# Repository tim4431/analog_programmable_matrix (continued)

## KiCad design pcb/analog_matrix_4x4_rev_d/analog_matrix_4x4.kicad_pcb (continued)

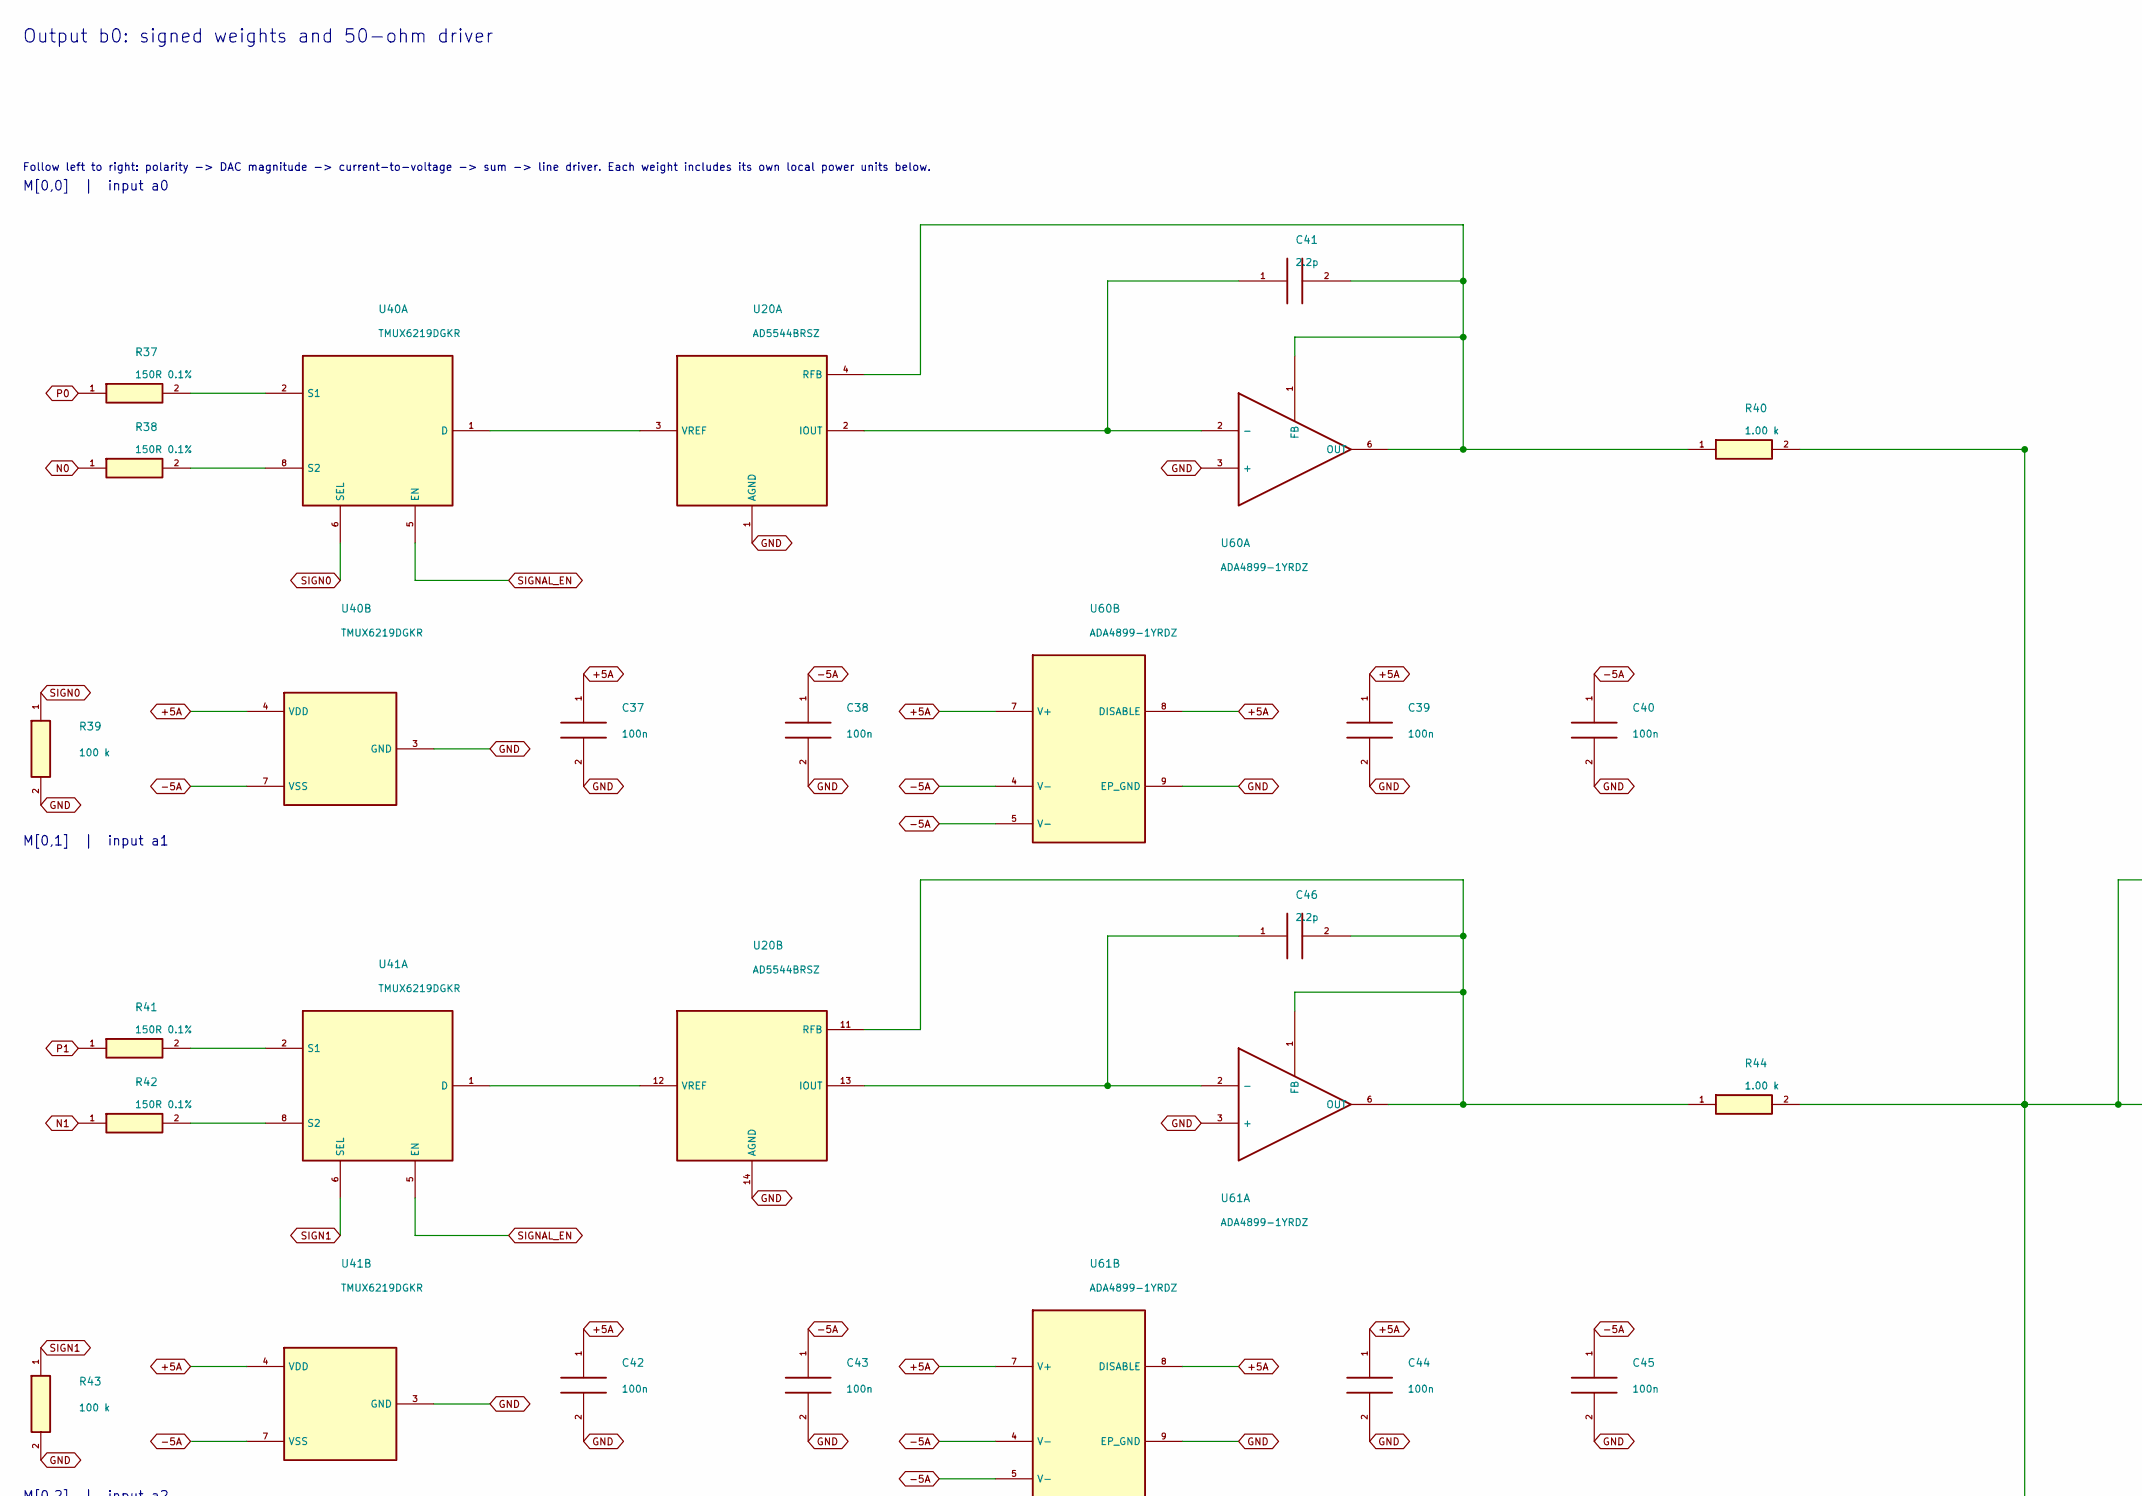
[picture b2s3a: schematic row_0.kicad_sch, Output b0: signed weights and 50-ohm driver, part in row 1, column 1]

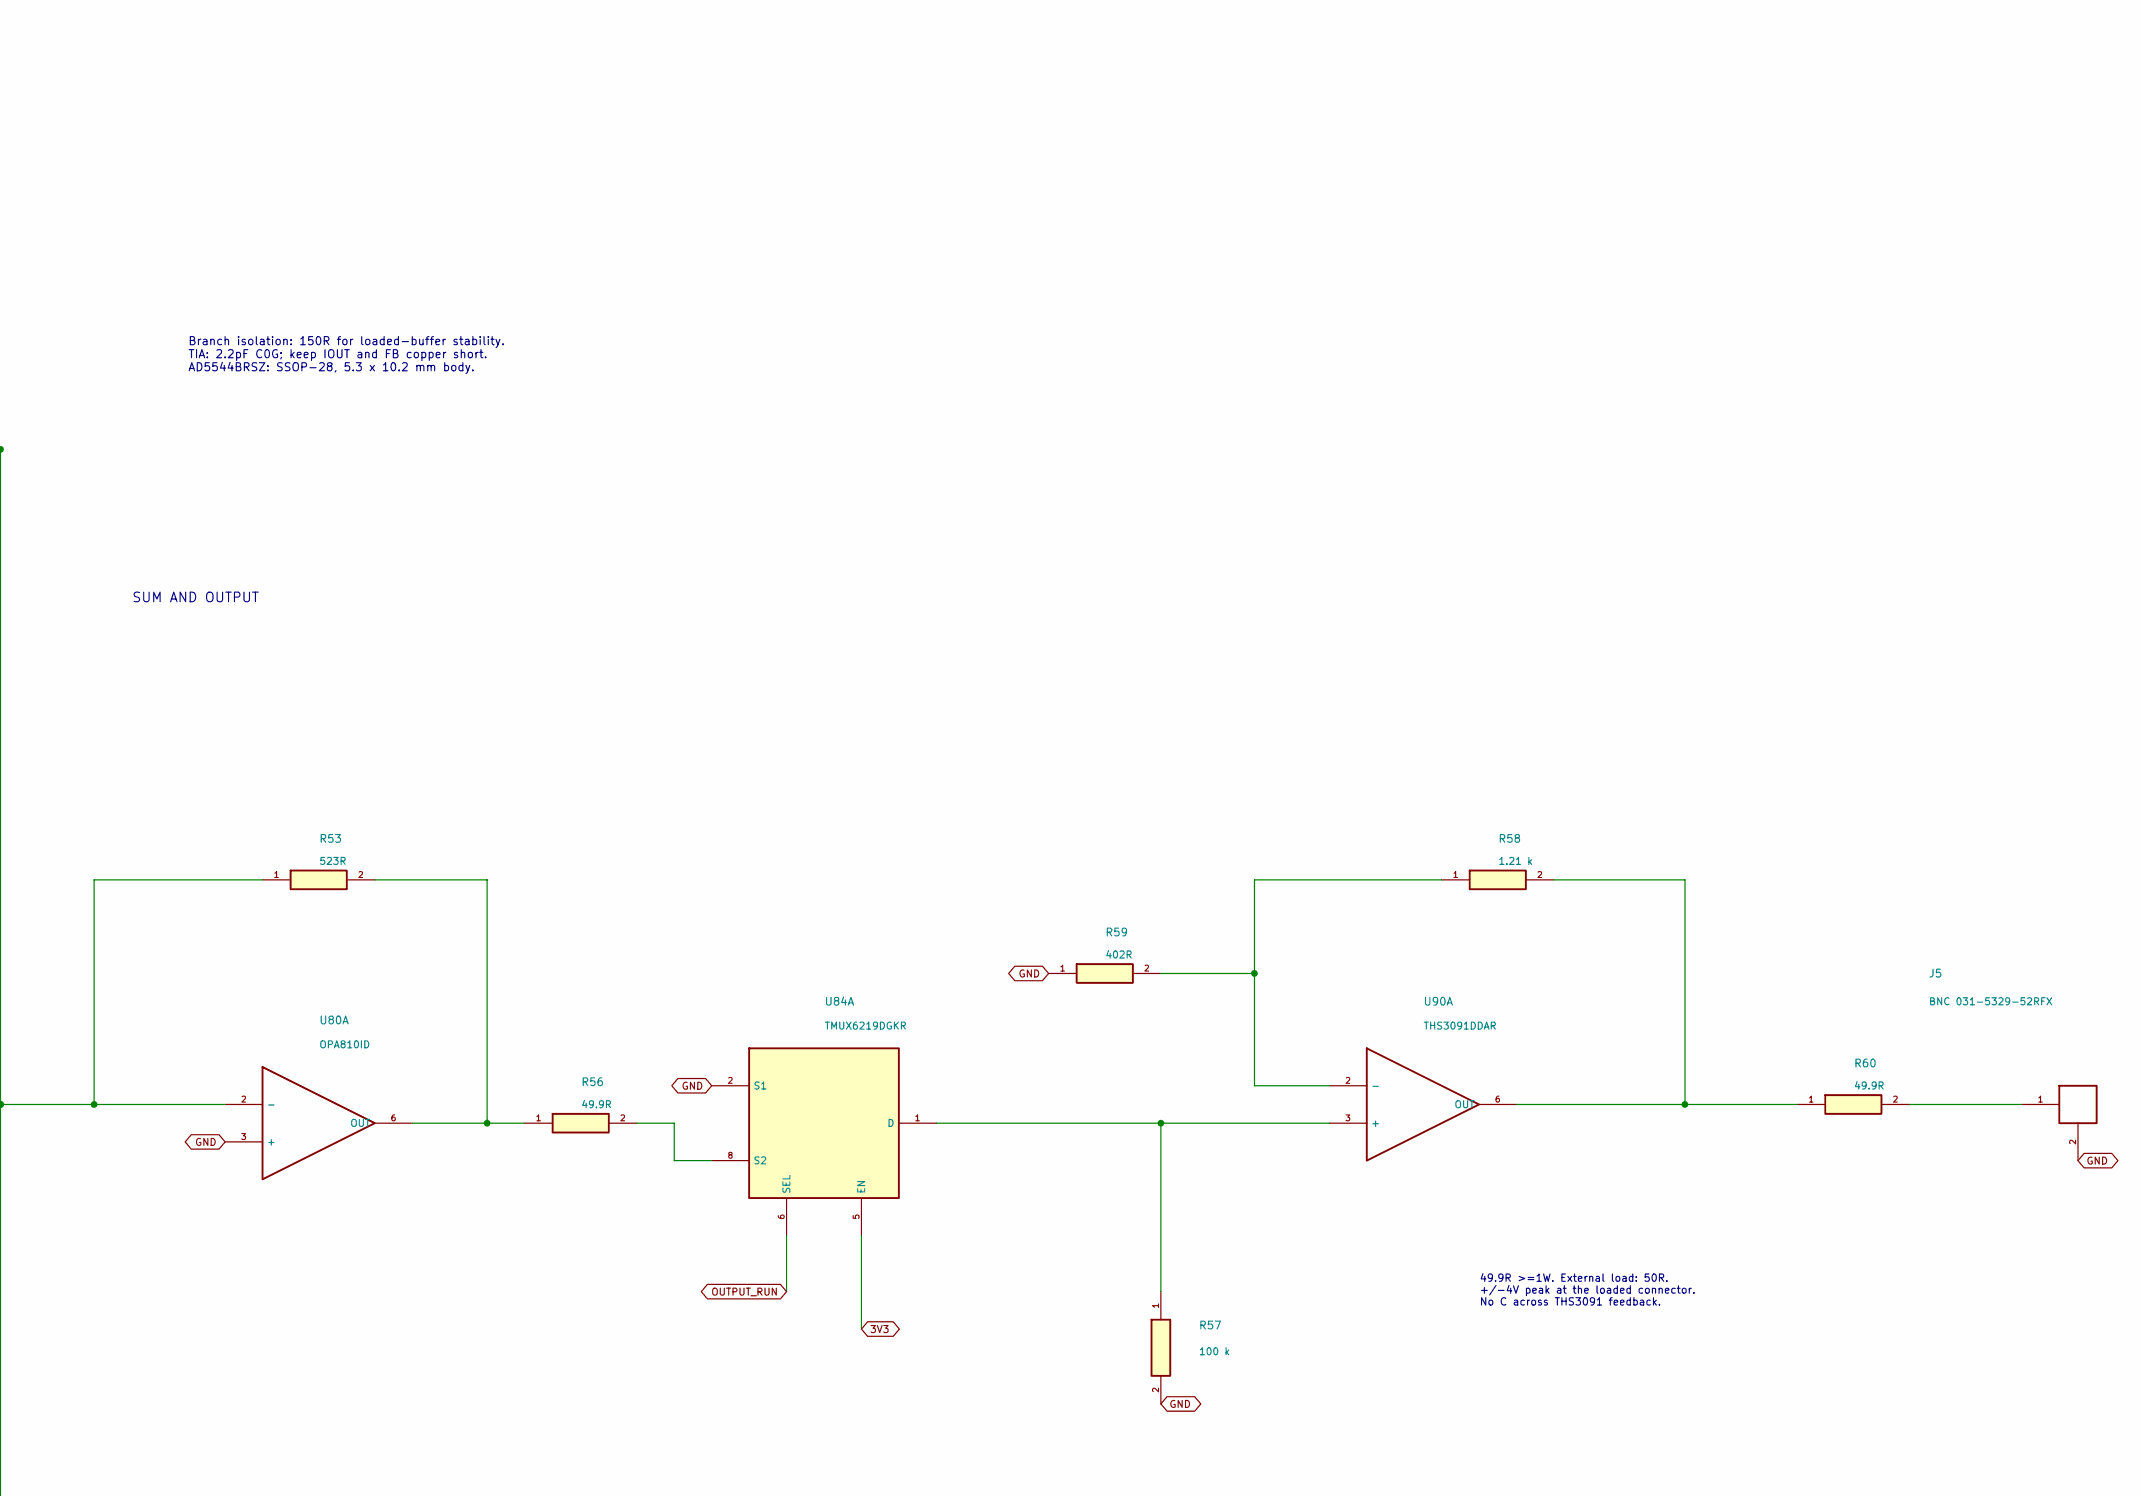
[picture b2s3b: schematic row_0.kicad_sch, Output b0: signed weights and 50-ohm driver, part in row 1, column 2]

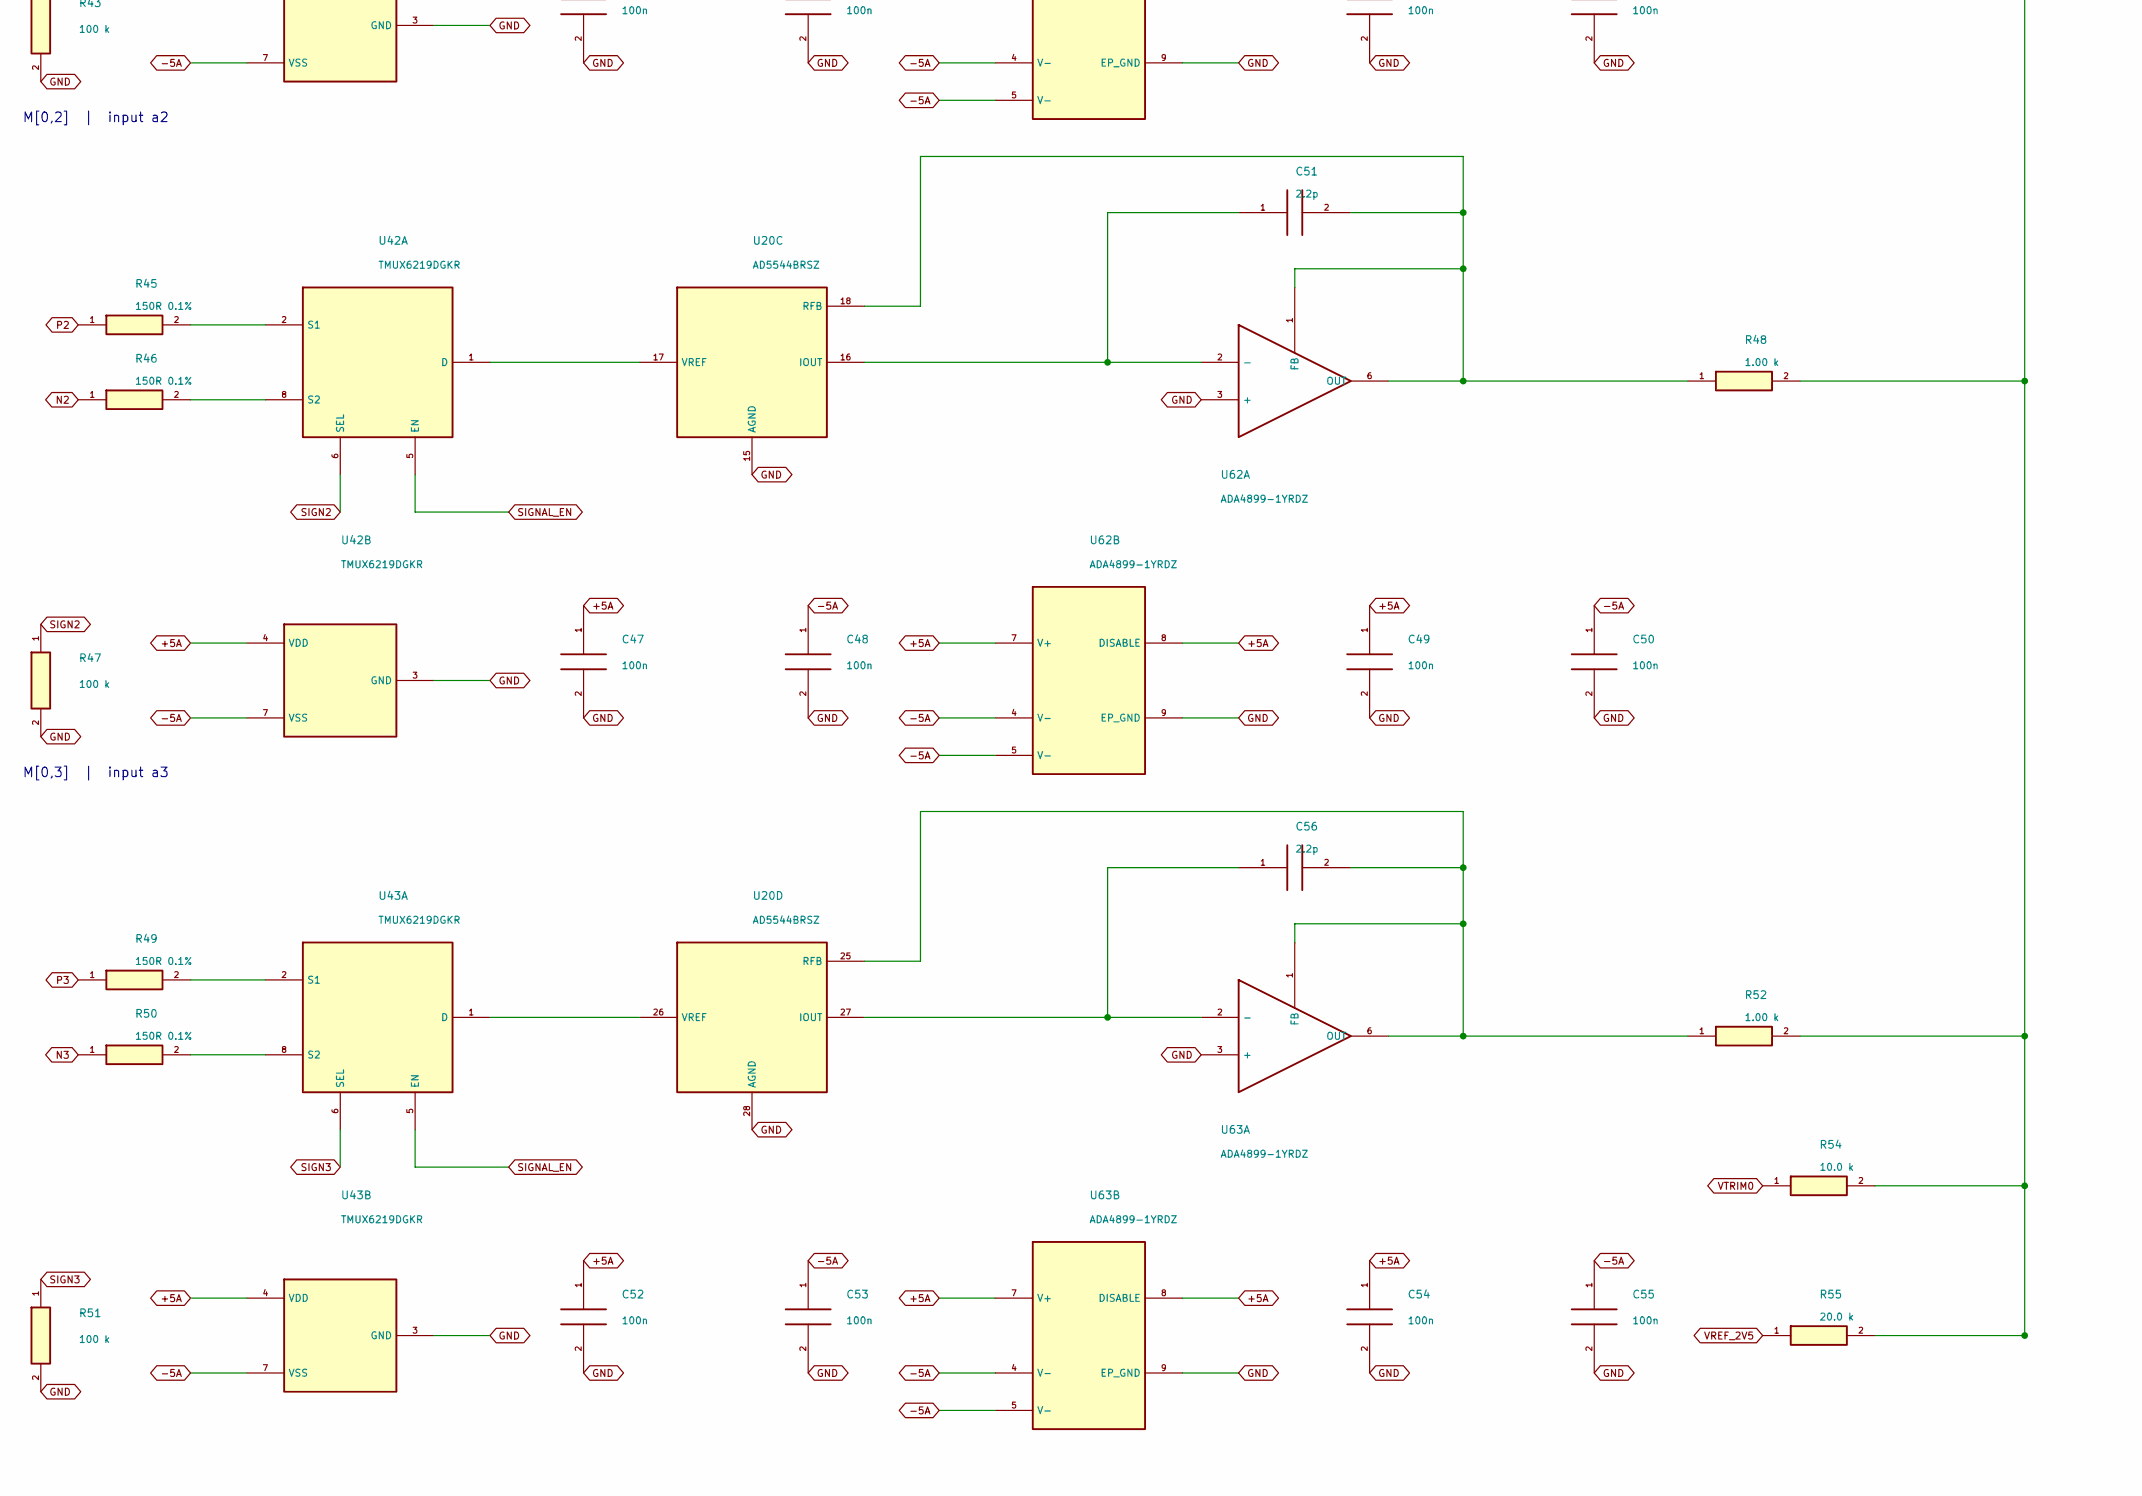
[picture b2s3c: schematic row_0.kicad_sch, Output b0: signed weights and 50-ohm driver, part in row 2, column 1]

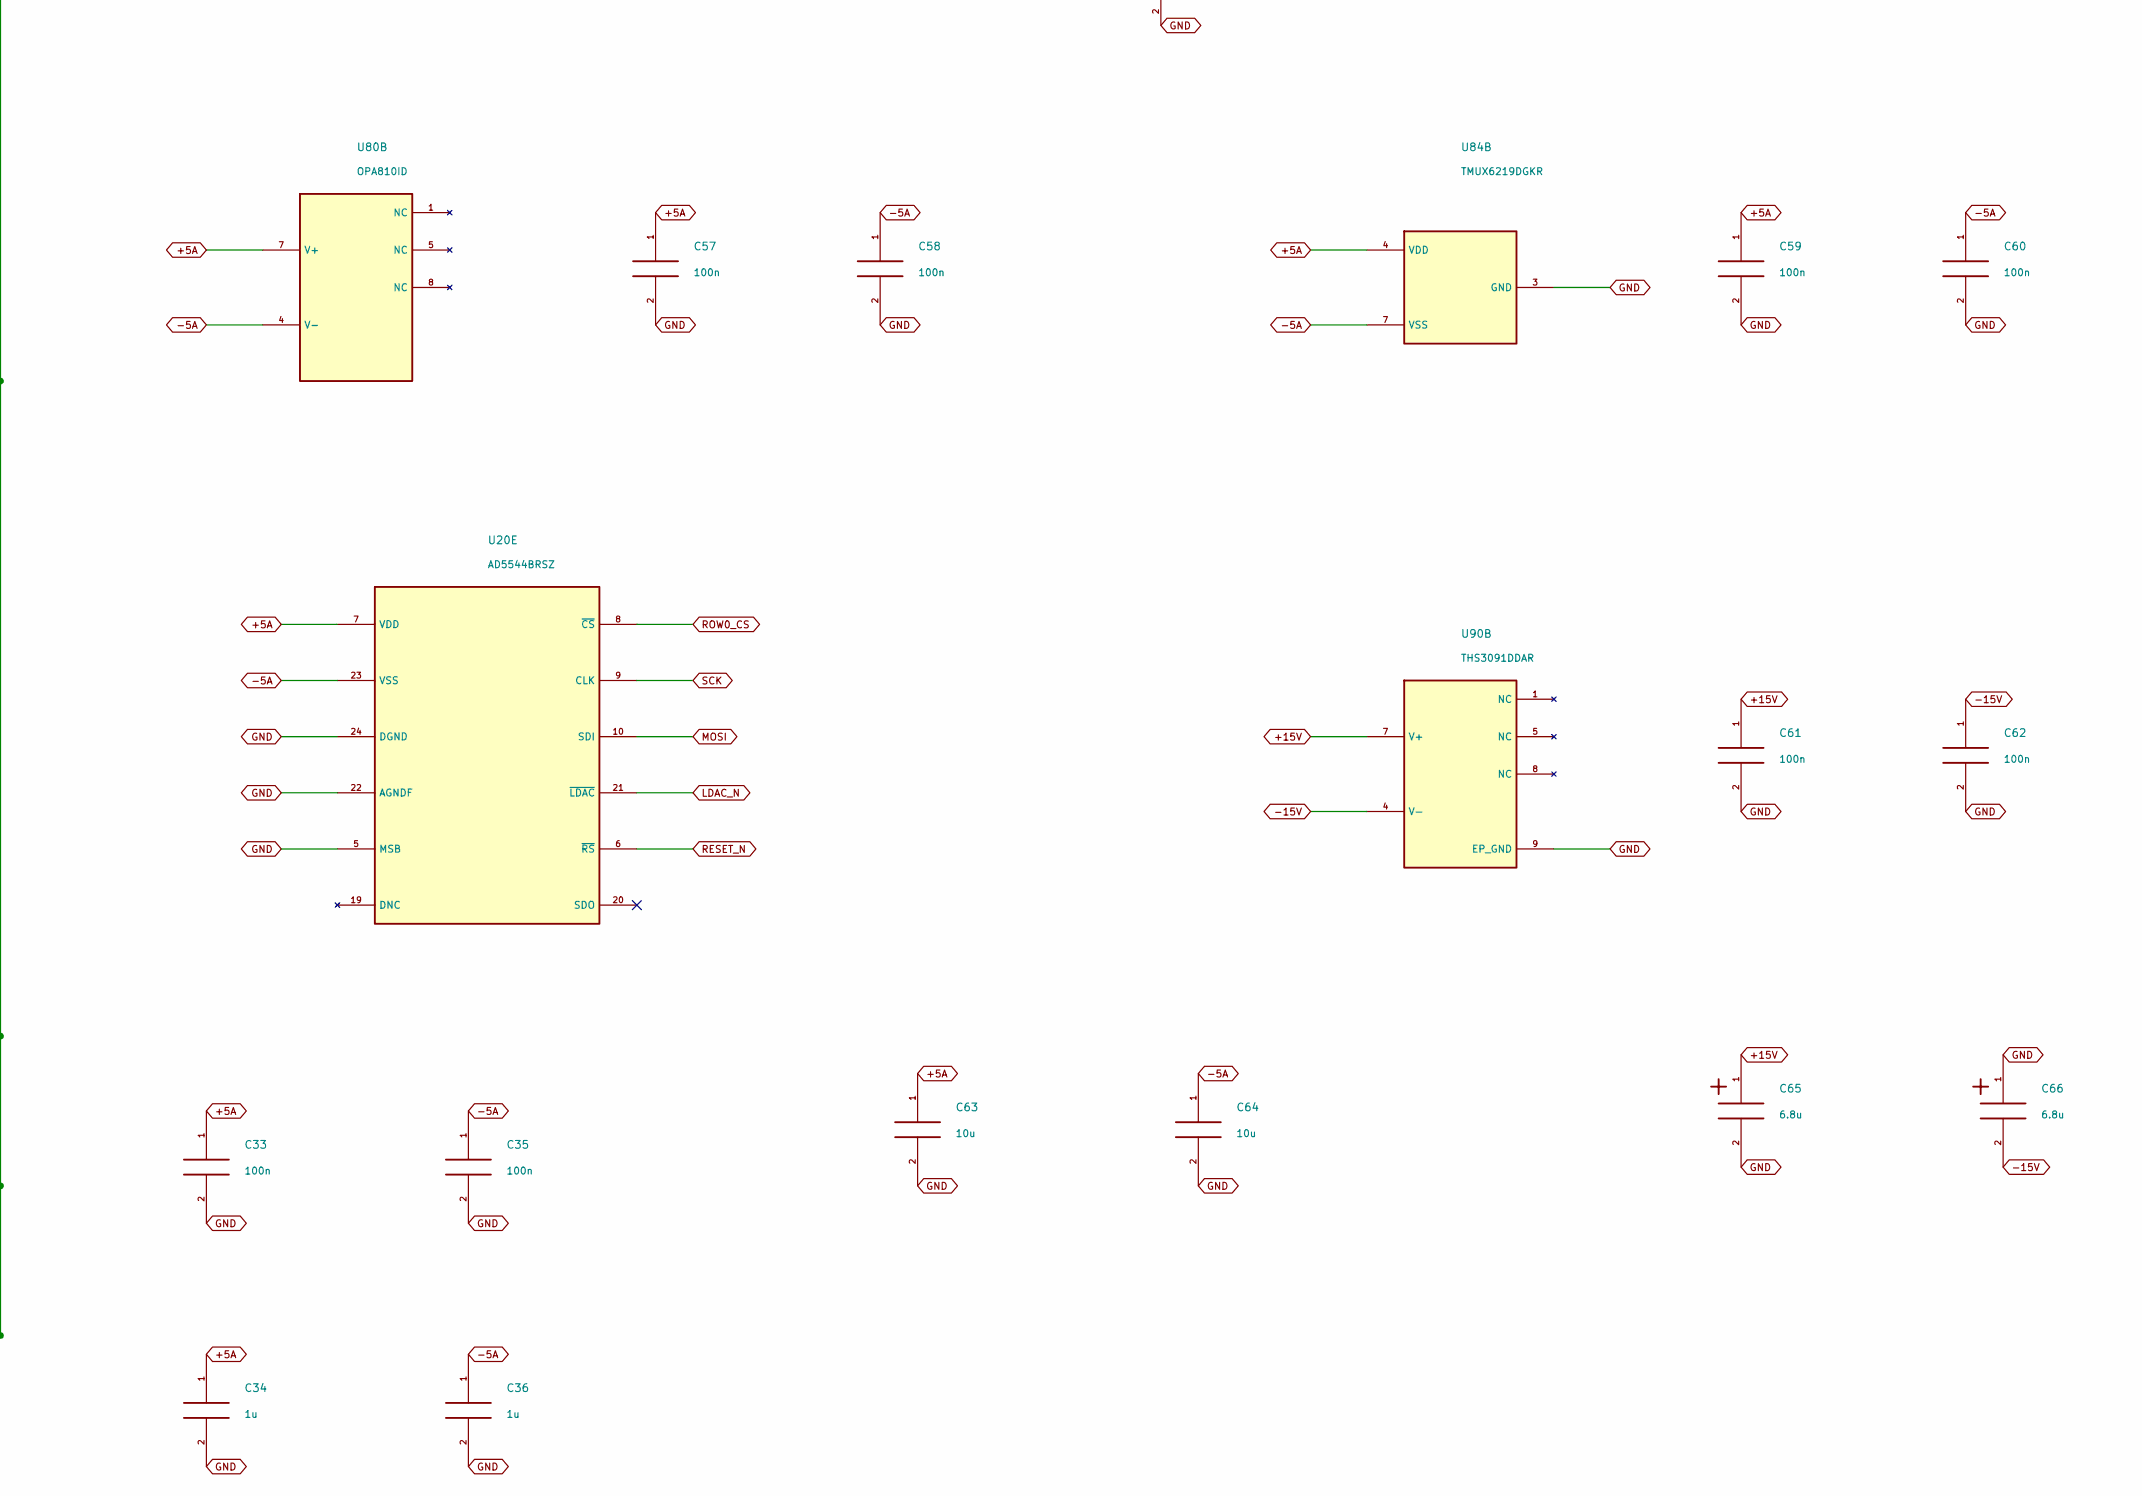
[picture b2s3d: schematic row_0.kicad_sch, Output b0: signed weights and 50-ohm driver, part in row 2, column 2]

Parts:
C33, C35, C37, C38, C39, C40, C42, C43, C44, C45, C47, C48, C49, C50, C52, C53, C54, C55, C57, C58, C59, C60, C61, C62: 100n; C_0603_1608Metric; Rating 25V X7R minimum; effective C after bias
C34, C36: 1u; C_0805_2012Metric; Rating 25V X7R minimum; effective C after bias
C41, C46, C51, C56: 2.2p; C_0402_1005Metric; Rating 50V C0G
C63, C64: 10u; C_0805_2012Metric; Rating 25V X7R minimum; effective C after bias
C65, C66: 6.8u; CP_EIA-3216-18_Kemet-A; Rating 25V polarized
J5: BNC 031-5329-52RFX; BNC_Amphenol_031-5329-52RFX_Vertical
R37, R38, R41, R42, R45, R46, R49, R50: 150R 0.1%; R_0603_1608Metric; Rating 0.1%, <=25ppm/C; 0.1W minimum
R39, R43, R47, R51, R57: 100 k; R_0603_1608Metric; Rating 0.1%, <=25ppm/C; 0.1W minimum
R40, R44, R48, R52: 1.00 k; R_0603_1608Metric; Rating 0.1%, <=25ppm/C; 0.1W minimum
R53: 523R; R_0603_1608Metric; Rating 0.1%, <=25ppm/C; 0.1W minimum
R54: 10.0 k; R_0603_1608Metric; Rating 0.1%, <=25ppm/C; 0.1W minimum
R55: 20.0 k; R_0603_1608Metric; Rating 0.1%, <=25ppm/C; 0.1W minimum
R56: 49.9R; R_0603_1608Metric; Rating 0.1%, <=25ppm/C; 0.1W minimum
R58: 1.21 k; R_0603_1608Metric; Rating 0.1%, <=25ppm/C; 0.1W minimum
R59: 402R; R_0603_1608Metric; Rating 0.1%, <=25ppm/C; 0.1W minimum
R60: 49.9R; R_2512_6332Metric; Rating 0.1%, <=25ppm/C; >=1W
U20: AD5544BRSZ; SSOP-28_5.3x10.2mm_P0.65mm
U40, U41, U42, U43, U84: TMUX6219DGKR; VSSOP-8_3x3mm_P0.65mm
U60, U61, U62, U63: ADA4899-1YRDZ; ADA4899_RD8_EP2.29x2.29
U80: OPA810ID; SOIC-8_3.9x4.9mm_P1.27mm
U90: THS3091DDAR; SOIC-8-1EP_3.9x4.9mm_P1.27mm_EP2.95x4.9mm_Mask2.71x3.4mm_Th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

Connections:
3V3: U84.5 (EN); also elsewhere on the board
+5A: C33.1, C34.1, C37.1, C39.1, C42.1, C44.1, C47.1, C49.1, C52.1, C54.1, C57.1, C59.1, C63.1, U20.7 (VDD), U40.4 (VDD), U41.4 (VDD), U42.4 (VDD), U43.4 (VDD), U60.7 (V+), U60.8 (DISABLE), U61.7 (V+), U61.8 (DISABLE), U62.7 (V+), U62.8 (DISABLE), U63.7 (V+), U63.8 (DISABLE), U80.7 (V+), U84.4 (VDD); also elsewhere on the board
+15V: C61.1, C65.1, U90.7 (V+); also elsewhere on the board
-5A: C35.1, C36.1, C38.1, C40.1, C43.1, C45.1, C48.1, C50.1, C53.1, C55.1, C58.1, C60.1, C64.1, U20.23 (VSS), U40.7 (VSS), U41.7 (VSS), U42.7 (VSS), U43.7 (VSS), U60.4 (V-), U60.5 (V-), U61.4 (V-), U61.5 (V-), U62.4 (V-), U62.5 (V-), U63.4 (V-), U63.5 (V-), U80.4 (V-), U84.7 (VSS); also elsewhere on the board
-15V: C62.1, C66.2, U90.4 (V-); also elsewhere on the board
GND: C33.2, C34.2, C35.2, C36.2, C37.2, C38.2, C39.2, C40.2, C42.2, C43.2, C44.2, C45.2, C47.2, C48.2, C49.2, C50.2, C52.2, C53.2, C54.2, C55.2, C57.2, C58.2, C59.2, C60.2, C61.2, C62.2, C63.2, C64.2, C65.2, C66.1, J5.2, R39.2, R43.2, R47.2, R51.2, R57.2, R59.1, U20.1 (AGND), U20.5 (MSB), U20.14 (AGND), U20.15 (AGND), U20.22 (AGNDF), U20.24 (DGND), U20.28 (AGND), U40.3 (GND), U41.3 (GND), U42.3 (GND), U43.3 (GND), U60.3 (+), U60.9 (EP_GND), U61.3 (+), U61.9 (EP_GND), U62.3 (+), U62.9 (EP_GND), U63.3 (+), U63.9 (EP_GND), U80.3 (+), U84.2 (S1), U84.3 (GND), U90.9 (EP_GND); also elsewhere on the board
LDAC_N: U20.21 (~LDAC); also elsewhere on the board
MOSI: U20.10 (SDI); also elsewhere on the board
N0: R38.1; also elsewhere on the board
N1: R42.1; also elsewhere on the board
N2: R46.1; also elsewhere on the board
N3: R50.1; also elsewhere on the board
unnamed: J5.1, R60.2
unnamed: C41.1, U20.2 (IOUT), U60.2 (-)
unnamed: C41.2, R40.1, U20.4 (RFB), U60.1 (FB), U60.6 (OUT)
unnamed: U20.3 (VREF), U40.1 (D)
unnamed: C46.1, U20.13 (IOUT), U61.2 (-)
unnamed: C46.2, R44.1, U20.11 (RFB), U61.1 (FB), U61.6 (OUT)
unnamed: U20.12 (VREF), U41.1 (D)
unnamed: C51.1, U20.16 (IOUT), U62.2 (-)
unnamed: C51.2, R48.1, U20.18 (RFB), U62.1 (FB), U62.6 (OUT)
unnamed: U20.17 (VREF), U42.1 (D)
unnamed: C56.1, U20.27 (IOUT), U63.2 (-)
unnamed: C56.2, R52.1, U20.25 (RFB), U63.1 (FB), U63.6 (OUT)
unnamed: U20.26 (VREF), U43.1 (D)
unnamed: R37.2, U40.2 (S1)
unnamed: R38.2, U40.8 (S2)
unnamed: R41.2, U41.2 (S1)
unnamed: R42.2, U41.8 (S2)
unnamed: R45.2, U42.2 (S1)
unnamed: R46.2, U42.8 (S2)
unnamed: R49.2, U43.2 (S1)
unnamed: R50.2, U43.8 (S2)
unnamed: R40.2, R44.2, R48.2, R52.2, R53.1, R54.2, R55.2, U80.2 (-)
unnamed: R53.2, R56.1, U80.6 (OUT)
unnamed: R57.1, U84.1 (D), U90.3 (+)
unnamed: R56.2, U84.8 (S2)
unnamed: R58.1, R59.2, U90.2 (-)
unnamed: R58.2, R60.1, U90.6 (OUT)
OUTPUT_RUN: U84.6 (SEL); also elsewhere on the board
P0: R37.1; also elsewhere on the board
P1: R41.1; also elsewhere on the board
P2: R45.1; also elsewhere on the board
P3: R49.1; also elsewhere on the board
RESET_N: U20.6 (~RS); also elsewhere on the board
ROW0_CS: U20.8 (~CS); also elsewhere on the board
SCK: U20.9 (CLK); also elsewhere on the board
SIGN0: R39.1, U40.6 (SEL); also elsewhere on the board
SIGN1: R43.1, U41.6 (SEL); also elsewhere on the board
SIGN2: R47.1, U42.6 (SEL); also elsewhere on the board
SIGN3: R51.1, U43.6 (SEL); also elsewhere on the board
SIGNAL_EN: U40.5 (EN), U41.5 (EN), U42.5 (EN), U43.5 (EN); also elsewhere on the board
VREF_2V5: R55.1; also elsewhere on the board
VTRIM0: R54.1; also elsewhere on the board

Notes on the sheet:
Output b0: signed weights and 50-ohm driver
Follow left to right: polarity -> DAC magnitude -> current-to-voltage -> sum -> line driver. Each weight includes its own local power units below.
M[0,0] | input a0
M[0,1] | input a1
M[0,2] | input a2
M[0,3] | input a3
SUM AND OUTPUT
49.9R >=1W. External load: 50R. +/-4V peak at the loaded connector. No C across THS3091 feedback.
Branch isolation: 150R for loaded-buffer stability. TIA: 2.2pF C0G; keep IOUT and FB copper short. AD5544BRSZ: SSOP-28, 5.3 x 10.2 mm body.
